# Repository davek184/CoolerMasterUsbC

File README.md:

# Cooler Master Novatouch Daughterboard USB-C
USB-C Daughterboard for Cooler Master Novatouch. Fits in the stock case without any changes.  Also fits Norbatouch, Masterkeys Pro S & Rapid-i.

Update 2026: This version is suprior but can be difficult to obtain so built an [alternative DIY option](https://github.com/davek184/Coolermaster-USB-C-remix)

## Disclaimers
* Norbatouch compatible if using 2 m3 nuts as washers.
* Use at your own risk
* This will only give USB-C connection for the keyboard. Programmability requires a custom full PCB.

# Cable
* JST SH to PH cable
* 5 pin
* 150mm long
* Good start cable
  * https://www.aliexpress.us/item/3256804552474270.html
  * "Same Direction" so only 2 wires need to be swapped after receiving. Plug in SH (small end) first. swap the D- and D+ wire on the PH end.
  * See pinout diagram
    
## Novatouch Pinout  

## Masterkeys Pro S Pinout

## Rapid-i Pinout

# Recommended Hardware

* M2 x 4mm wafer head screw/laptop screw. For mounting CMDB into stock Novatouch case. https://www.aliexpress.us/item/3256801240948974.html 
* M3 x 0.5mm 6mm hex screw, 3mm hex nut. For mounting CMDB into Norbatouch. Add o-ring or washer if still sitting too low in port opening.
* [Alternative 3d print riser](/assets/Coolermaster%20USB%20C%20Riser.stl)

# Installation Photos

<details>
 <summary>Stock Novatouch</summary>

</details>

<details>
 <summary>Norbatouch PC</summary>

</details>

<details>
 <summary>Norbatouch Aluminum </summary>

</details>

# Revisions
* 1.1 Lets not dwell on version 1.1 other than it paved the way for version 1.2 :)
* 1.2 Worked successfully with Novatouch and Norbatouch
* 1.3 Updated design to include extra size for manufacturing along with a dummy resistor on the backside
* 1.4 Removed extra rails manufacturing because they wanted to charge extra claiming 2 designs in one file

# Manufacturing
<details>
  <summary>JLCPCB</summary>
 
  * Files: [/manufacturing](/manufacturing)
  * **1mm thick** (NOT Standard 1.6mm)
  * SMD Assembly is **Standard** not economic due to USB connector
  * Confirm Parts Placement: **Yes**
</details>
<details>
  <summary>BOM</summary>

| LCSC part # | Description        | Value | Package  | Amount |
| ----------- | ------------------ | ----- | -------- | ------ |
| C67381      | Connector (USB)    |       | SMD      | 1      |
| C136657     | Connector(JST SH)  | 5 pin | TH       | 1      |
| C7519       | ESD                |       | SOT23-6  | 1      |
| C261942     | Fuse               |       | 0805     | 1      |
| C597300     | Capacitor          | 4.7nF | 0805     | 1      |
| C212411     | Resistor           | 5.1K  | 0805     | 1      |
</details>

# Acknowledgments 
* [Nekotato](/https://github.com/nekotato) for validating compatibility and requesting this
* [Gouty](/https://github.com/Gouty) for initial measurements from repo: https://github.com/Gouty/CM-Keyboard_USB-Breakout
* Pixelpusher for validating compatibility in Novatouch, Masterkeys Pro S & Rapid-i.

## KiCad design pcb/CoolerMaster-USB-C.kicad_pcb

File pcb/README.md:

Replacement USB-C daughterboard for FC980m/c can be used with the stock case or Norbauer Heavy-9.

_Note stock case requires filing USB opening and cable is tight._

## BOM

| LCSC part # | Description   | Value | Package  | Amount |
| ----------- | ------------- | ----- | -------- | ------:|
| C165948     | USB           |       | SMD/TH   | 1      |
| C160404     | Connector     |       | SMD      | 1      |
| C528030     | Connector     |       | SMD      | 1      |
| C261942     | Fuse	      |       | SMD      | 1      |
| C27834      | Resistor      | 5.1   | SMD      | 2      |
| C7519       | ESD           |       | SMD      | 1      |

## Cable

This daughterboard uses a different connector then the OEM one. Suggest starting with an [Adafruit 4424 cable](https://www.adafruit.com/product/4424) so no crimping needs to be done.

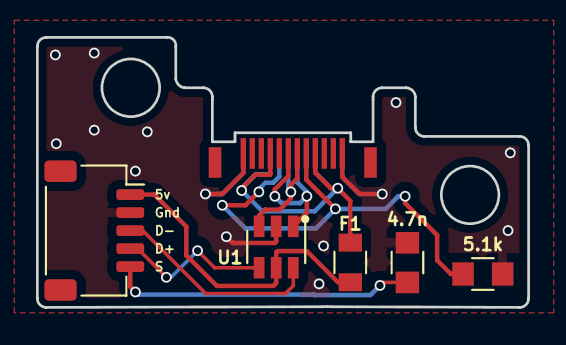
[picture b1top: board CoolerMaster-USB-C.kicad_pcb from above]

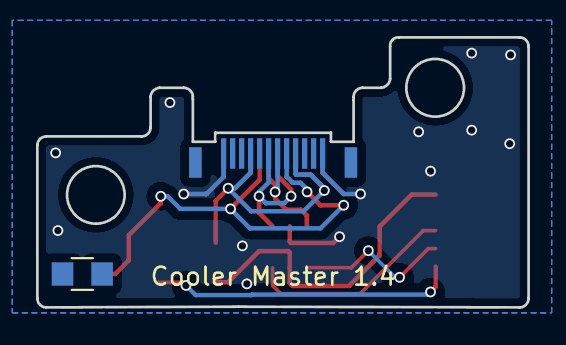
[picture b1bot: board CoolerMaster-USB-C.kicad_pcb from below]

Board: 2 copper layers, 27.3 x 15.0 mm, 8 parts (2 on the bottom side), 7 nets.

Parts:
C1: 4.7n; R_0805
F1: Polyfuse_Small; F_0805
G3: LOGO; MegaMan7
J1: USB-C-SMD_C67381
J2: JST_SH_SM05B-SRSS-TB_1x05-1MP_P1.00mm_Horizontal
R2: 5.1k; R_0805
R2#2: R_0805
U1: USBLC6-2SC6

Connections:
D+: J2.4, U1.4 (I/O2)
D-: J2.3, U1.6 (I/O1)
GND: C1.1, J1.1, J1.13, J2.2, R2.2, U1.2 (GND)
unnamed: J1.6, U1.1 (I/O1)
unnamed: J1.7, U1.3 (I/O2)
unnamed: J1.8, R2.1
VBUS: F1.1, F1.2, J1.4, J1.9, J2.1, U1.5 (VBUS)

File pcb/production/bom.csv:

Designator,Footprint,Quantity,Value,LCSC Part #
C1,R_0805,1,4.7n,
F1,F_0805,1,Polyfuse_Small,
J1,USB-C-SMD_C67381,1,USB-C-SMD_C67381,
J2,JST_SH_SM05B-SRSS-TB_1x05-1MP_P1.00mm_Horizontal,1,JST_SH_SM05B-SRSS-TB_1x05-1MP_P1.00mm_Horizontal,
R2_2,R_0805,1,5.1k,
R2,R_0805,1,,
U1,USBLC6-2SC6,1,USBLC6-2SC6,

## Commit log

2023-06-29 Initial Push
2023-07-03 PCB files
2023-07-07 Fixed cable
2023-07-14 Revision 1.3
2023-07-14 Add files via upload
    temporary views of mounting in Norbatouch. m3 nuts adaptation by goguma.
2023-07-16 Version 1.4
    Version 1.4
2023-08-12 Add files via upload
    JST cable setups for Novatouch, Masterkeys Pro S / Rapid-i keyboards
2023-08-12 Merge pull request #1 from davek184/nekotato-patch-1
    Add files via upload
2023-08-19 Update README.md
    Removed original cable because it is confusing vs the new images
2024-05-25 Add files via upload
    cable order for rapid-i is similar to masterkeys pro s except for switching the D- and D+
2024-05-25 Rename rapid-i.JPG to rapidIcablenew.JPG
2026-02-15 Add update on alternative DIY option for daughterboard
    Added update note about alternative DIY option for USB-C daughterboard.
2026-02-15 Add alternative 3D print riser to hardware recommendations
